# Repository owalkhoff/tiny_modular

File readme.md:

# tinyModular

## What is this project about?

This is a modular synthesizer built around the ATtiny microcontroller. All modules have identical hardware, and can be programmed to become oscillators, filters, noise generators, etc.

This project is based on the original miniMO by Jose Gonzalez: [minimosynth.com](https://minimosynth.com). Software and instructions can be found there too.

## Design goals for the first version

Edition One is my first attempt to create a [Eurorack](https://en.wikipedia.org/wiki/Eurorack) module based on the original miniMO. The goal was to create a module that can be quickly and easily built using DIY methods, on a single PCB, with as few as possible through hole components, no vias and without wiring. The schematic was redrawn from the original by Jose Gonzalez.

## Images

Here is an image of the first built module:

Here is a rendering of the PCB, with some components:

## PDFs

The PCB layout used for printing on transparency film:

[tiny_modular_pcb.pdf](edition_one/pdf/tiny_modular_pcb.pdf)

The schematic:

[tiny_modular_schematic.pdf](edition_one/pdf/tiny_modular_schematic.pdf)

## KiCad files

The schematic and layout were drawn in KiCad 5.0.2. You can find the project [in this directory](edition_one/kicad_5).

## Caveats

~~The 3.5mm jacks should be positioned perpendicularly to the module front in order to be accessible, but there seems to be no jack on the market which can do this. A solution might be to add an auxiliary PCB for the jacks, soldered to the main PCB perpendicularly.~~

This has now been solved with Thonkiconn vertical 3.5mm jack sockets (PJ398SM) by thonk.co.uk, thanks to dusjagr. Bend pin 3 by 90 degrees so that it can be soldered to the pad smd style.

~~Pin 1 (J3) and pin 6 (J4) are still unconnected on this revision of the PCB. The idea is that pin 6 supplies power to the PCB when it is connected to a programmer with the jumper set for this on J3.~~

Fixed in this revision.

## License

The tinyModular circuit is CC NC BY minimosynth.com

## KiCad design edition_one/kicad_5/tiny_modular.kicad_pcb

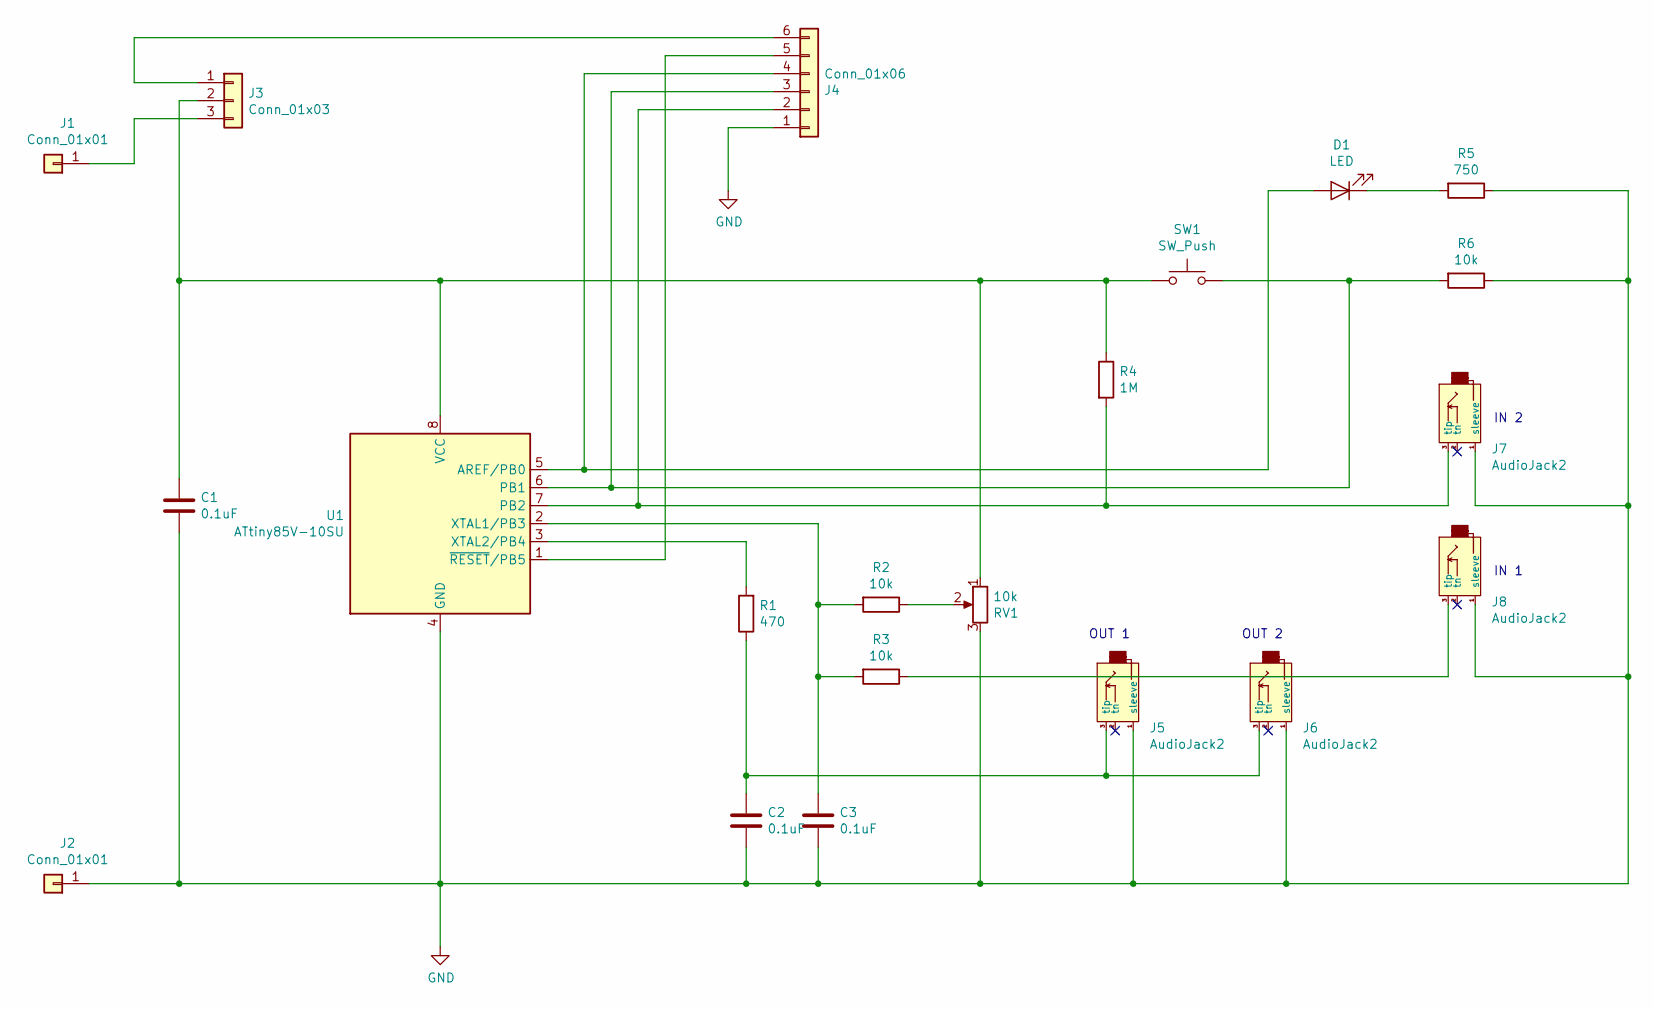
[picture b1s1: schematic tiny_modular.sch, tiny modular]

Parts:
C1, C2, C3: 0.1uF; C_1206_3216Metric_Pad1.42x1.75mm_HandSolder
D1: LED; LED_PLCC-2
J1, J2: Conn_01x01; SolderWirePad_1x01_Drill1mm
J3: Conn_01x03; PinHeader_1x03_P2.54mm_Vertical
J4: Conn_01x06; PinHeader_1x06_P2.54mm_Vertical
J5, J6, J7, J8: AudioJack2; PJ301M-12_bent
R1: 470; R_1206_3216Metric_Pad1.42x1.75mm_HandSolder
R2, R3, R6: 10k; R_1206_3216Metric_Pad1.42x1.75mm_HandSolder
R4: 1M; R_1206_3216Metric_Pad1.42x1.75mm_HandSolder
R5: 750; R_1206_3216Metric_Pad1.42x1.75mm_HandSolder
RV1: 10k; Potentiometer_Alps_RK09K_Single_Vertical
SW1: SW_Push; SW_SPST_EVQQ2
U1: ATtiny85V-10SU; DIP-8_W7.62mm_LongPads

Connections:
GND: C1.2, C2.1, C3.2, J2.1, J4.1, J5.1 (sleeve), J6.1 (sleeve), J7.1 (sleeve), J8.1 (sleeve), R5.1, R6.1, RV1.3, U1.4 (GND)
unnamed: C1.1, J3.2, R4.1, RV1.1, SW1.1, U1.8 (VCC)
unnamed: C2.2, J5.3 (tip), J6.3 (tip), R1.1
unnamed: C3.1, R2.2, R3.2, U1.2 (XTAL1/PB3)
unnamed: D1.1 (K), R5.2
unnamed: D1.2 (A), J4.4, U1.5 (AREF/PB0)
unnamed: J1.1, J3.3
unnamed: J3.1, J4.6
unnamed: J4.2, J7.3 (tip), R4.2, U1.7 (PB2)
unnamed: J4.3, R6.2, SW1.2, U1.6 (PB1)
unnamed: J4.5, U1.1 (~RESET~/PB5)
unnamed: J8.3 (tip), R3.1
unnamed: R1.2, U1.3 (XTAL2/PB4)
unnamed: R2.1, RV1.2

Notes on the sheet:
IN 1
IN 2
OUT 2
OUT 1

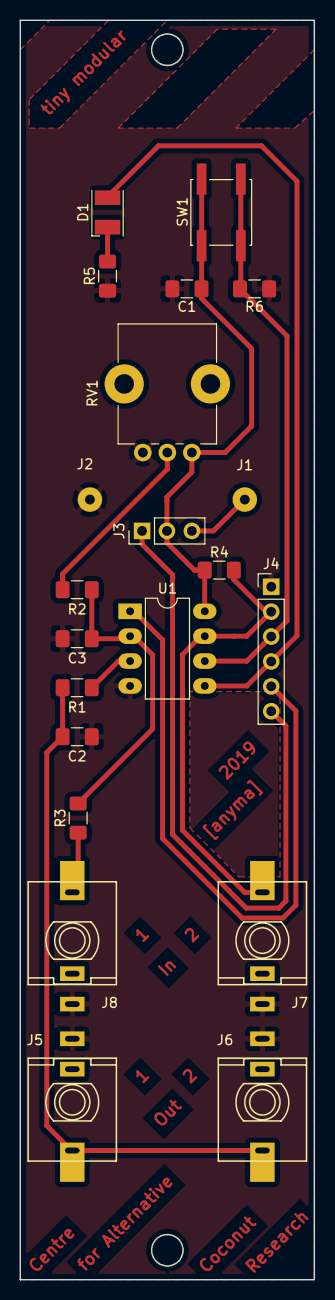
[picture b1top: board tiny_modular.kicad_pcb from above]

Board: 2 copper layers, 30.0 x 128.5 mm, 21 parts (0 on the bottom side), 14 nets.

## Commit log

2019-06-04 Revision anyma 2019 with vertical jack sockets
